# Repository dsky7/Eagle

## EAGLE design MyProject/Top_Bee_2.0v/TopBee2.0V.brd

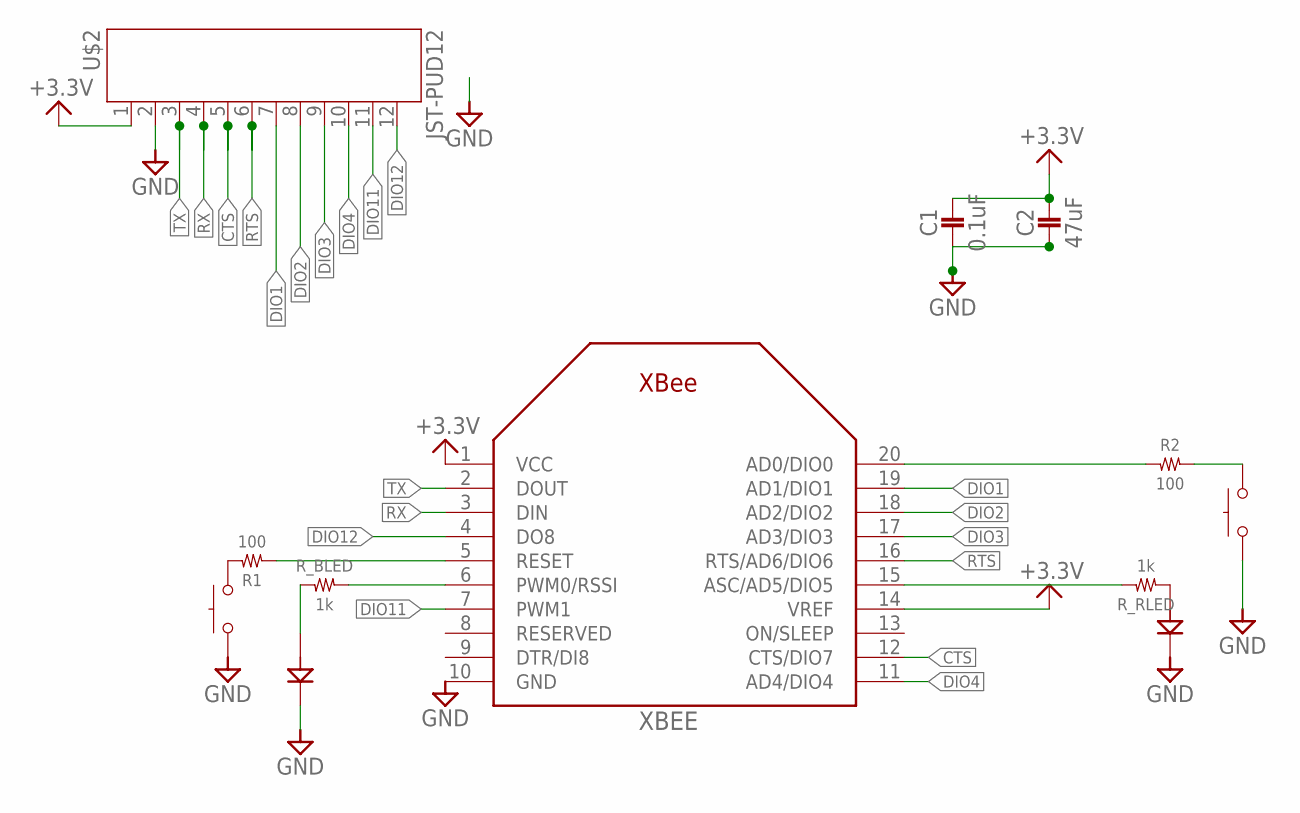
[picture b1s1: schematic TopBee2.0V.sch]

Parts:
C1: 0.1uF; 1608
C2: 47uF; 3225
COMM: SKRPACE010; SKRP
LED_B: 1608
LED_R: 1608
R1, R2: 100; 1608
RESET: SKRPACE010; SKRP
R_BLED: 1k; 1608
R_RLED: 1k; 1608
U$2: JST-PUD12
XBEE: XBEE

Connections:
+3.3V: C1.P$1 (1), C2.P$1 (1), U$2.1, XBEE.1 (VCC), XBEE.14 (VREF)
CTS: U$2.5, XBEE.12 (CTS/DIO7)
DIO1: U$2.7, XBEE.19 (AD1/DIO1)
DIO2: U$2.8, XBEE.18 (AD2/DIO2)
DIO3: U$2.9, XBEE.17 (AD3/DIO3)
DIO4: U$2.10, XBEE.11 (AD4/DIO4)
DIO11: U$2.11, XBEE.7 (PWM1)
DIO12: U$2.12, XBEE.4 (DO8)
GND: C1.P$2 (2), C2.P$2 (2), COMM.3, COMM.4, LED_B.2 (K), LED_R.2 (K), RESET.3, RESET.4, U$2.2, XBEE.10 (GND)
unnamed: LED_R.1 (A), R_RLED.1
unnamed: R2.1, XBEE.20 (AD0/DIO0)
unnamed: R1.1, XBEE.5 (RESET)
unnamed: R1.2, RESET.1, RESET.2
unnamed: COMM.1, COMM.2, R2.2
unnamed: R_BLED.2, XBEE.6 (PWM0/RSSI)
unnamed: R_RLED.2, XBEE.15 (ASC/AD5/DIO5)
unnamed: LED_B.1 (A), R_BLED.1
RTS: U$2.6, XBEE.16 (RTS/AD6/DIO6)
RX: U$2.4, XBEE.3 (DIN)
TX: U$2.3, XBEE.2 (DOUT)

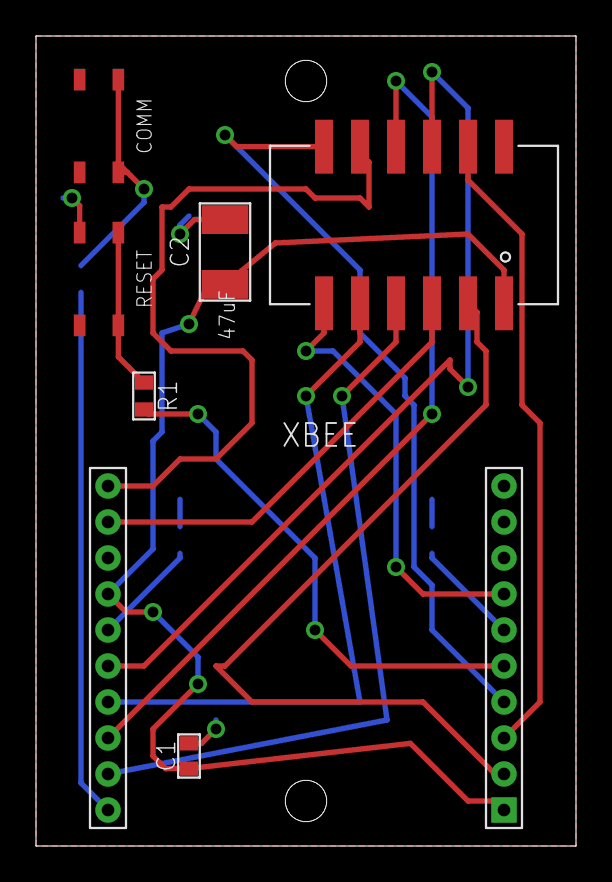
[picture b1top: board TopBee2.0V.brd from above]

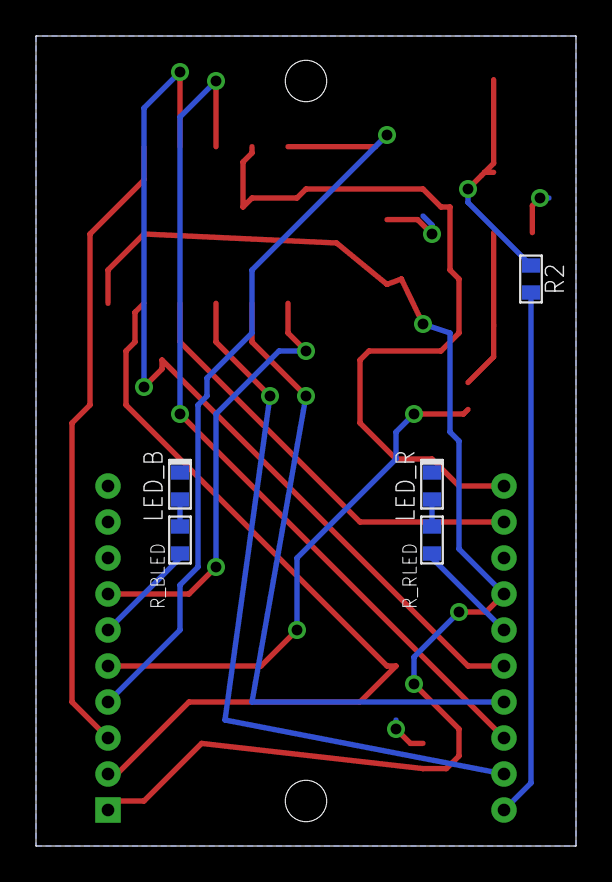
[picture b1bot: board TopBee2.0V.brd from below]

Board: 2 copper layers, 30.0 x 45.0 mm, 12 parts (5 on the bottom side), 20 nets.

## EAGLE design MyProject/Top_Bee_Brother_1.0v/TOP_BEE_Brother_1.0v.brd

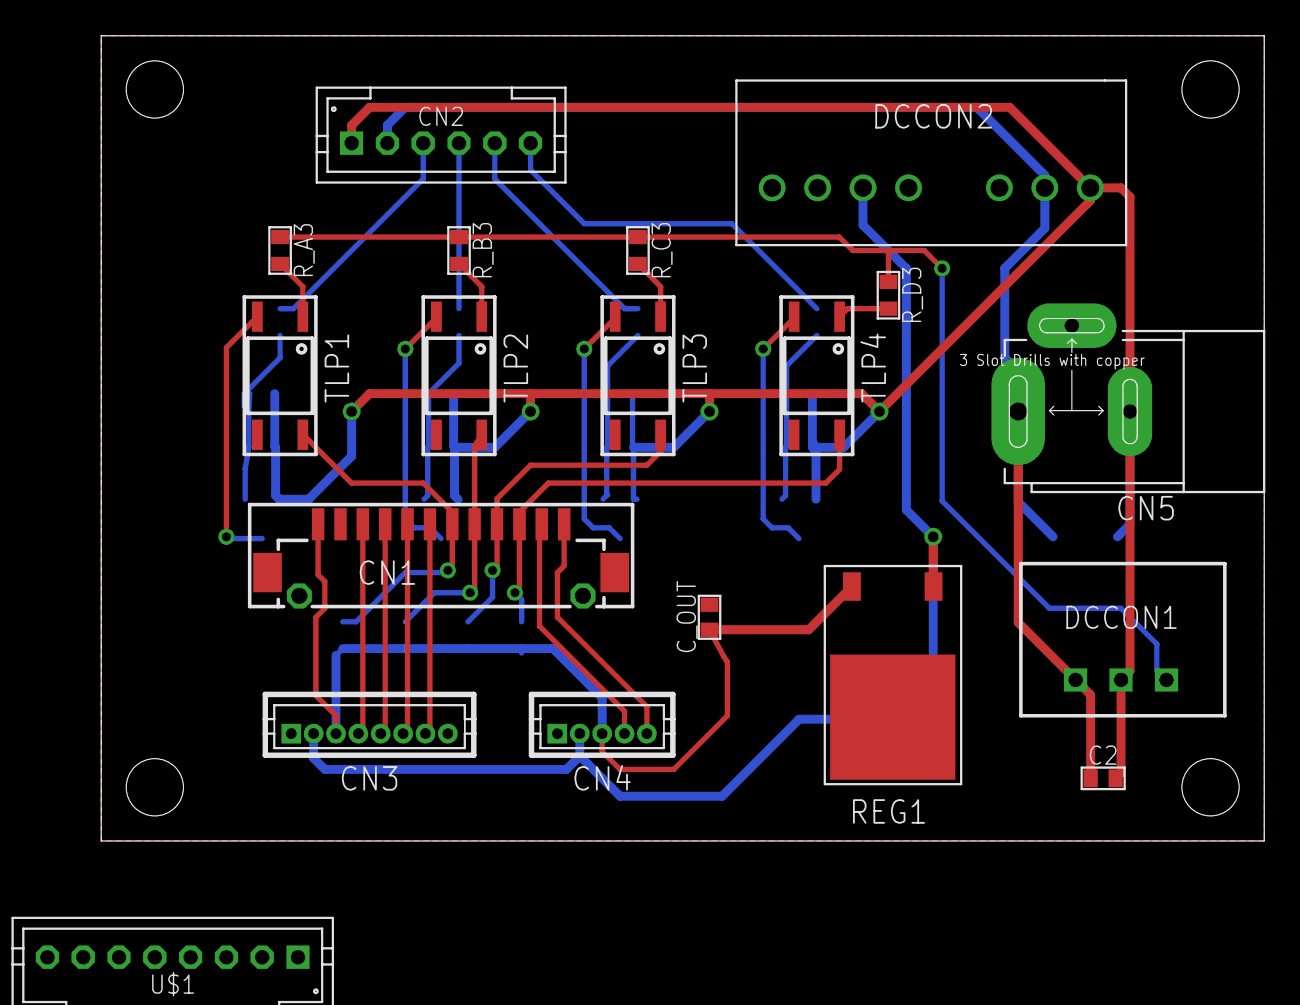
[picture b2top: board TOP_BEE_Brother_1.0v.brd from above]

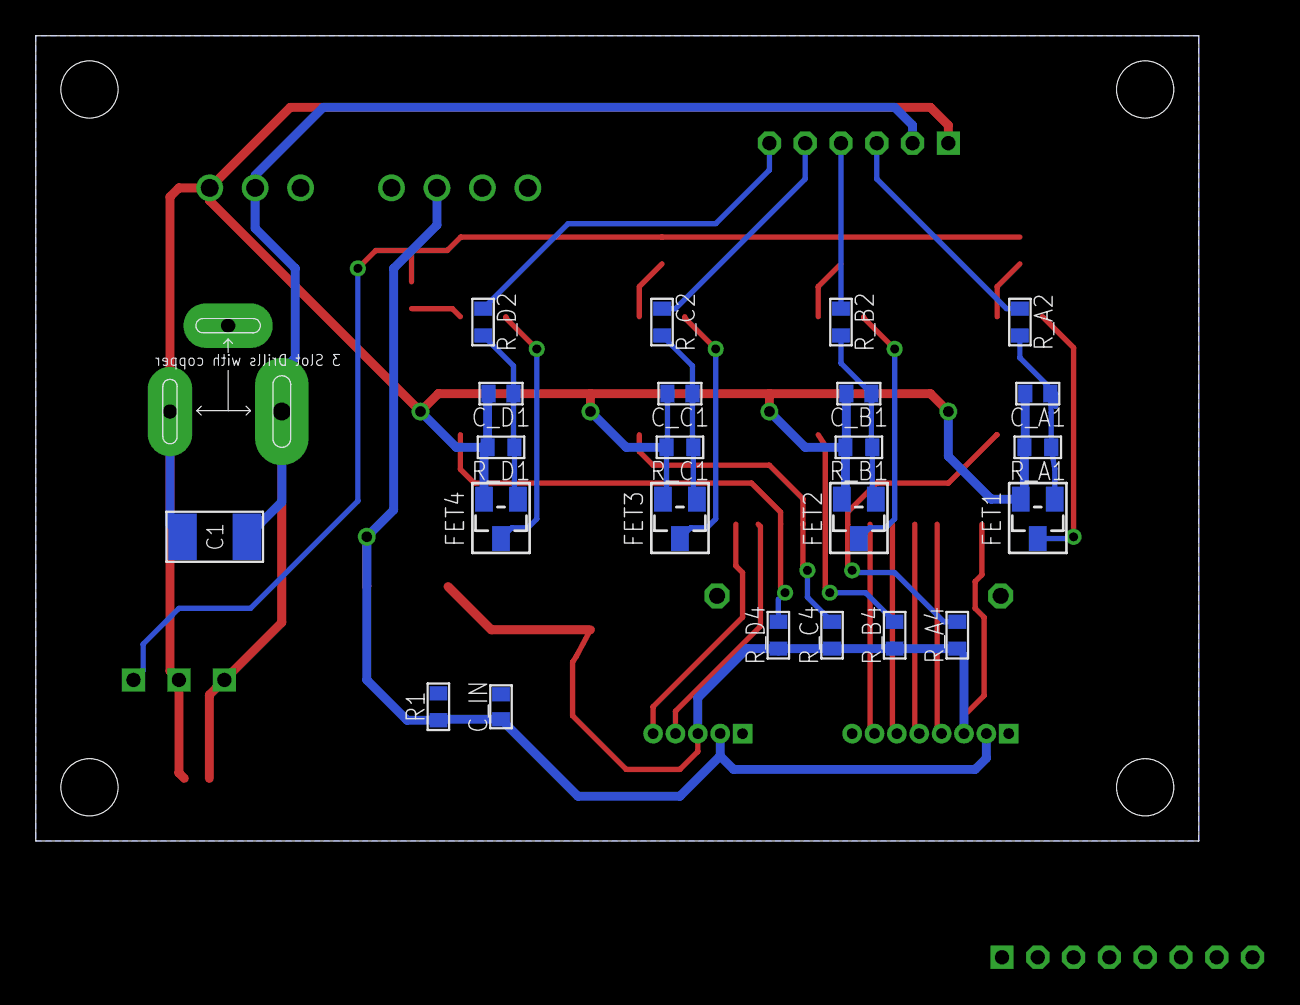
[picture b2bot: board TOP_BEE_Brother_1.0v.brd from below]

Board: 2 copper layers, 65.0 x 45.0 mm, 42 parts (23 on the bottom side), 32 nets.

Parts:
C1: 3225
C2: 1608
CN1: DF13-12P-1.25V; DF13C-12P-1.25V
CN2: JST-PA6
CN3: DF13-8P-1.25DSA
CN4: DF13-5P-1.25DSA
CN5: 2DC-0005X; 2DC-0005D
C_A1: 1608
C_B1: 1608
C_C1: 1608
C_D1: 1608
C_IN: 1608
C_OUT: 1608
DCCON1: Ｒ－７８Ｅ５．０
DCCON2: RS3; SIP8
FET1, FET2, FET3, FET4: 2N7002K; SOT23
R1: 1608
REG1: NJM2845; TO252
R_A1: 4.7K; 1608
R_A2, R_A4: 10k; 1608
R_A3: 330; 1608
R_B1: 4.7K; 1608
R_B2: 10K; 1608
R_B3: 330; 1608
R_B4: 10k; 1608
R_C1: 4.7K; 1608
R_C2: 10K; 1608
R_C3: 330; 1608
R_C4: 10k; 1608
R_D1: 4.7K; 1608
R_D2: 10K; 1608
R_D3: 330; 1608
R_D4: 10k; 1608
TLP1, TLP2, TLP3, TLP4: TLP124; 11−4C1
U$1: JST-PA8

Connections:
2N7002K: C_A1.P$1, FET1.1, R_A1.2, R_A2.1
+3.3V: CN1.P$1, CN3.P$3, CN4.P$3, C_OUT.P$1, REG1.3, R_A4.2, R_B4.2, R_C4.2, R_D4.2
+5V: CN3.P$2, CN4.P$2, C_IN.P$1, DCCON2.6, R1.2, REG1.1
+24V: C1.P$1, C2.P$1, CN2.2, CN5.1, DCCON1.1, DCCON2.2
CTS: CN1.P$5, CN3.P$6
DIO1: CN1.P$7, R_A4.1, TLP1.6
DIO2: CN1.P$8, R_B4.1, TLP2.6
DIO3: CN1.P$9, R_C4.1, TLP3.6
DIO4: CN1.P$10, R_D4.1, TLP4.6
DIO11: CN1.P$11, CN4.P$4
DIO12: CN1.P$12, CN4.P$5
GND: CN1.G1, CN1.G2, CN1.M$0, CN1.M$1, CN1.P$2, CN3.P$1, CN4.P$1, C_IN.P$2, C_OUT.P$2, DCCON2.7, R1.1, REG1.2, TLP1.4, TLP2.4, TLP3.4, TLP4.4
GND2: C1.P$2, C2.P$2, CN2.1, CN5.2, C_A1.P$2, C_B1.P$2, C_C1.P$2, C_D1.P$2, DCCON1.2, DCCON2.1, FET1.2, FET2.2, FET3.2, FET4.2, R_A1.1, R_B1.1, R_C1.1, R_D1.1
INPUT1: CN2.3, R_A2.2
INPUT2: CN2.4, R_B2.2
INPUT3: CN2.5, R_C2.2
INPUT4: CN2.6, R_D2.2
unnamed: FET2.3, TLP2.3
unnamed: FET1.3, TLP1.3
unnamed: R_A3.1, TLP1.1
unnamed: FET4.3, TLP4.3
unnamed: R_B3.1, TLP2.1
unnamed: C_B1.P$1, FET2.1, R_B1.2, R_B2.1
unnamed: FET3.3, TLP3.3
unnamed: R_C3.1, TLP3.1
unnamed: C_C1.P$1, FET3.1, R_C1.2, R_C2.1
unnamed: R_D3.1, TLP4.1
unnamed: C_D1.P$1, FET4.1, R_D1.2, R_D2.1
RTS: CN1.P$6, CN3.P$7
RX: CN1.P$4, CN3.P$5
TX: CN1.P$3, CN3.P$4
V2: DCCON1.3, R_A3.2, R_B3.2, R_C3.2, R_D3.2

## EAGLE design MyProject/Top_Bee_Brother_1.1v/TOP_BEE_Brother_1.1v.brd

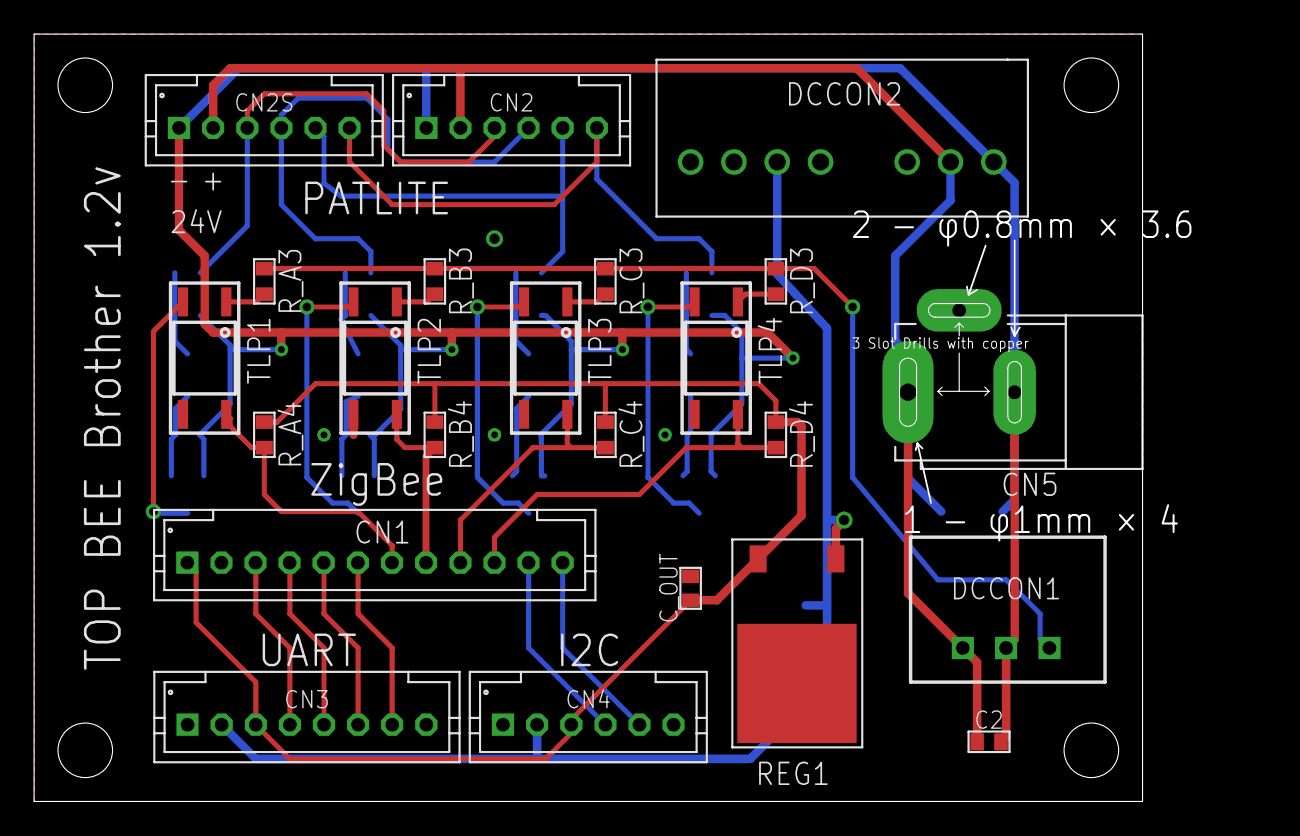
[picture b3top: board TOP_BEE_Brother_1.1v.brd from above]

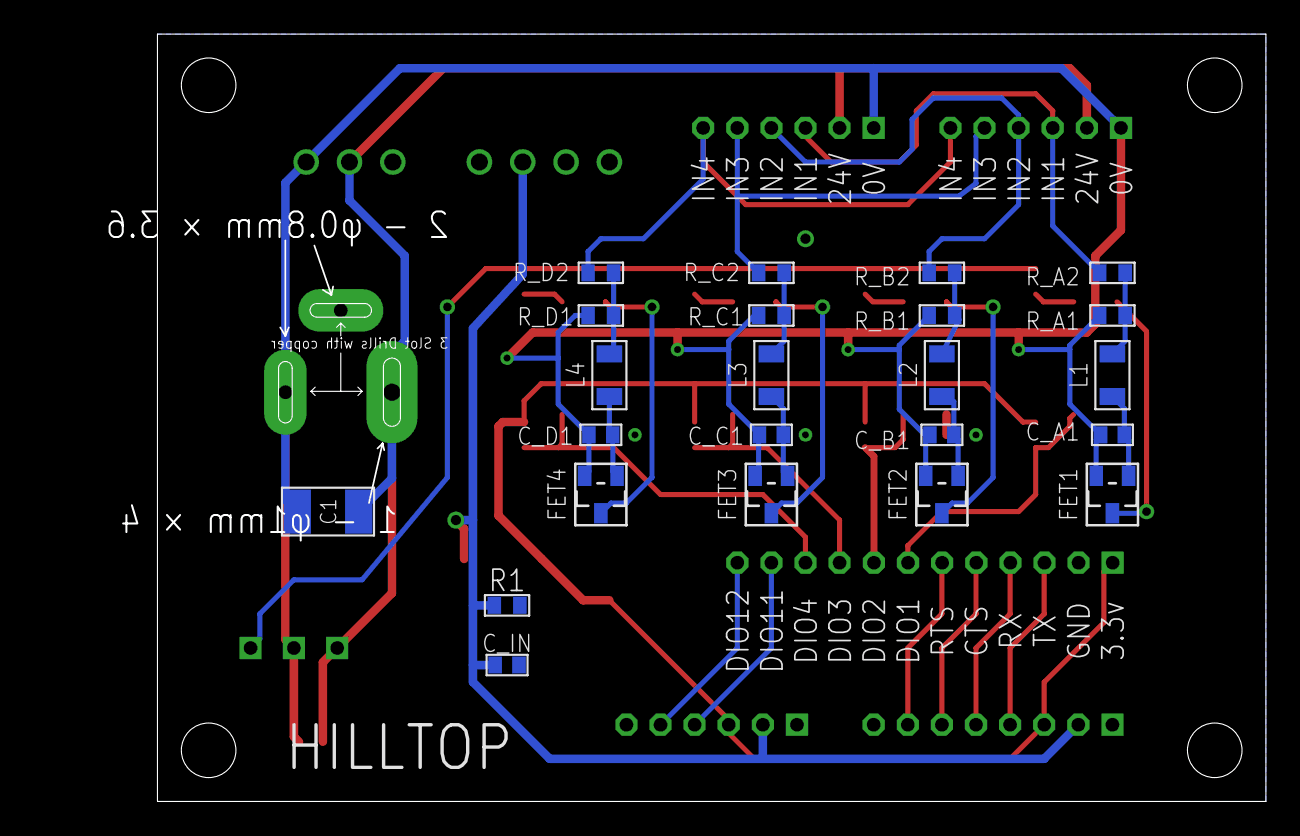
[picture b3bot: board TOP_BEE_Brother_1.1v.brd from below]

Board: 2 copper layers, 65.0 x 45.0 mm, 47 parts (23 on the bottom side), 36 nets.

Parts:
C1: 3225
C2: 1608
CN1: JST-PA12
CN2, CN2S, CN4: JST-PA6
CN3: JST-PA8
CN5: 2DC-0005X; 2DC-0005D
C_A1: 1608
C_B1: 1608
C_C1: 1608
C_D1: 1608
C_IN: 1608
C_OUT: 1608
DCCON1: Ｒ－７８Ｅ５．０
DCCON2: RS3; SIP8
DRILEGEND: DRILEGEND
FET1, FET2, FET3, FET4: 2N7002K; SOT23
L1, L2, L3, L4: TDK_NLV25; TDK_NLV
R1: 1608
REG1: NJM2845; TO252
R_A1: 4.7K; 1608
R_A2, R_A4: 10k; 1608
R_A3: 330; 1608
R_B1: 4.7K; 1608
R_B2: 10K; 1608
R_B3: 330; 1608
R_B4: 10k; 1608
R_C1: 4.7K; 1608
R_C2: 10K; 1608
R_C3: 330; 1608
R_C4: 10k; 1608
R_D1: 4.7K; 1608
R_D2: 10K; 1608
R_D3: 330; 1608
R_D4: 10k; 1608
TLP1, TLP2, TLP3, TLP4: TLP124; 11−4C1

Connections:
2N7002K: L1.P$1, R_A1.2, R_A2.1
+3.3V: CN1.1, CN3.3, CN4.3, C_OUT.P$1, REG1.3, R_A4.2, R_B4.2, R_C4.2, R_D4.2
+5V: CN3.2, CN4.2, C_IN.P$1, DCCON2.6, R1.2, REG1.1
+24V: C1.P$1, C2.P$1, CN2.2, CN2S.2, CN5.1, DCCON1.1, DCCON2.2
CTS: CN1.5, CN3.6
DIO1: CN1.7, R_A4.1, TLP1.6
DIO2: CN1.8, R_B4.1, TLP2.6
DIO3: CN1.9, R_C4.1, TLP3.6
DIO4: CN1.10, R_D4.1, TLP4.6
DIO11: CN1.11, CN4.4
DIO12: CN1.12, CN4.5
GND: CN1.2, CN3.1, CN4.1, C_IN.P$2, C_OUT.P$2, DCCON2.7, R1.1, REG1.2, TLP1.4, TLP2.4, TLP3.4, TLP4.4
GND2: C1.P$2, C2.P$2, CN2.1, CN2S.1, CN5.2, C_A1.P$2, C_B1.P$2, C_C1.P$2, C_D1.P$2, DCCON1.2, DCCON2.1, FET1.2, FET2.2, FET3.2, FET4.2, R_A1.1, R_B1.1, R_C1.1, R_D1.1
INPUT1: CN2.3, CN2S.3, R_A2.2
INPUT2: CN2.4, CN2S.4, R_B2.2
INPUT3: CN2.5, CN2S.5, R_C2.2
INPUT4: CN2.6, CN2S.6, R_D2.2
unnamed: FET2.3, TLP2.3
unnamed: FET1.3, TLP1.3
unnamed: R_A3.1, TLP1.1
unnamed: FET4.3, TLP4.3
unnamed: R_B3.1, TLP2.1
unnamed: L2.P$1, R_B1.2, R_B2.1
unnamed: FET3.3, TLP3.3
unnamed: R_C3.1, TLP3.1
unnamed: L3.P$1, R_C1.2, R_C2.1
unnamed: R_D3.1, TLP4.1
unnamed: L4.P$1, R_D1.2, R_D2.1
unnamed: C_A1.P$1, FET1.1, L1.P$2
unnamed: C_B1.P$1, FET2.1, L2.P$2
unnamed: C_C1.P$1, FET3.1, L3.P$2
unnamed: C_D1.P$1, FET4.1, L4.P$2
RTS: CN1.6, CN3.7
RX: CN1.4, CN3.5
TX: CN1.3, CN3.4
V2: DCCON1.3, R_A3.2, R_B3.2, R_C3.2, R_D3.2

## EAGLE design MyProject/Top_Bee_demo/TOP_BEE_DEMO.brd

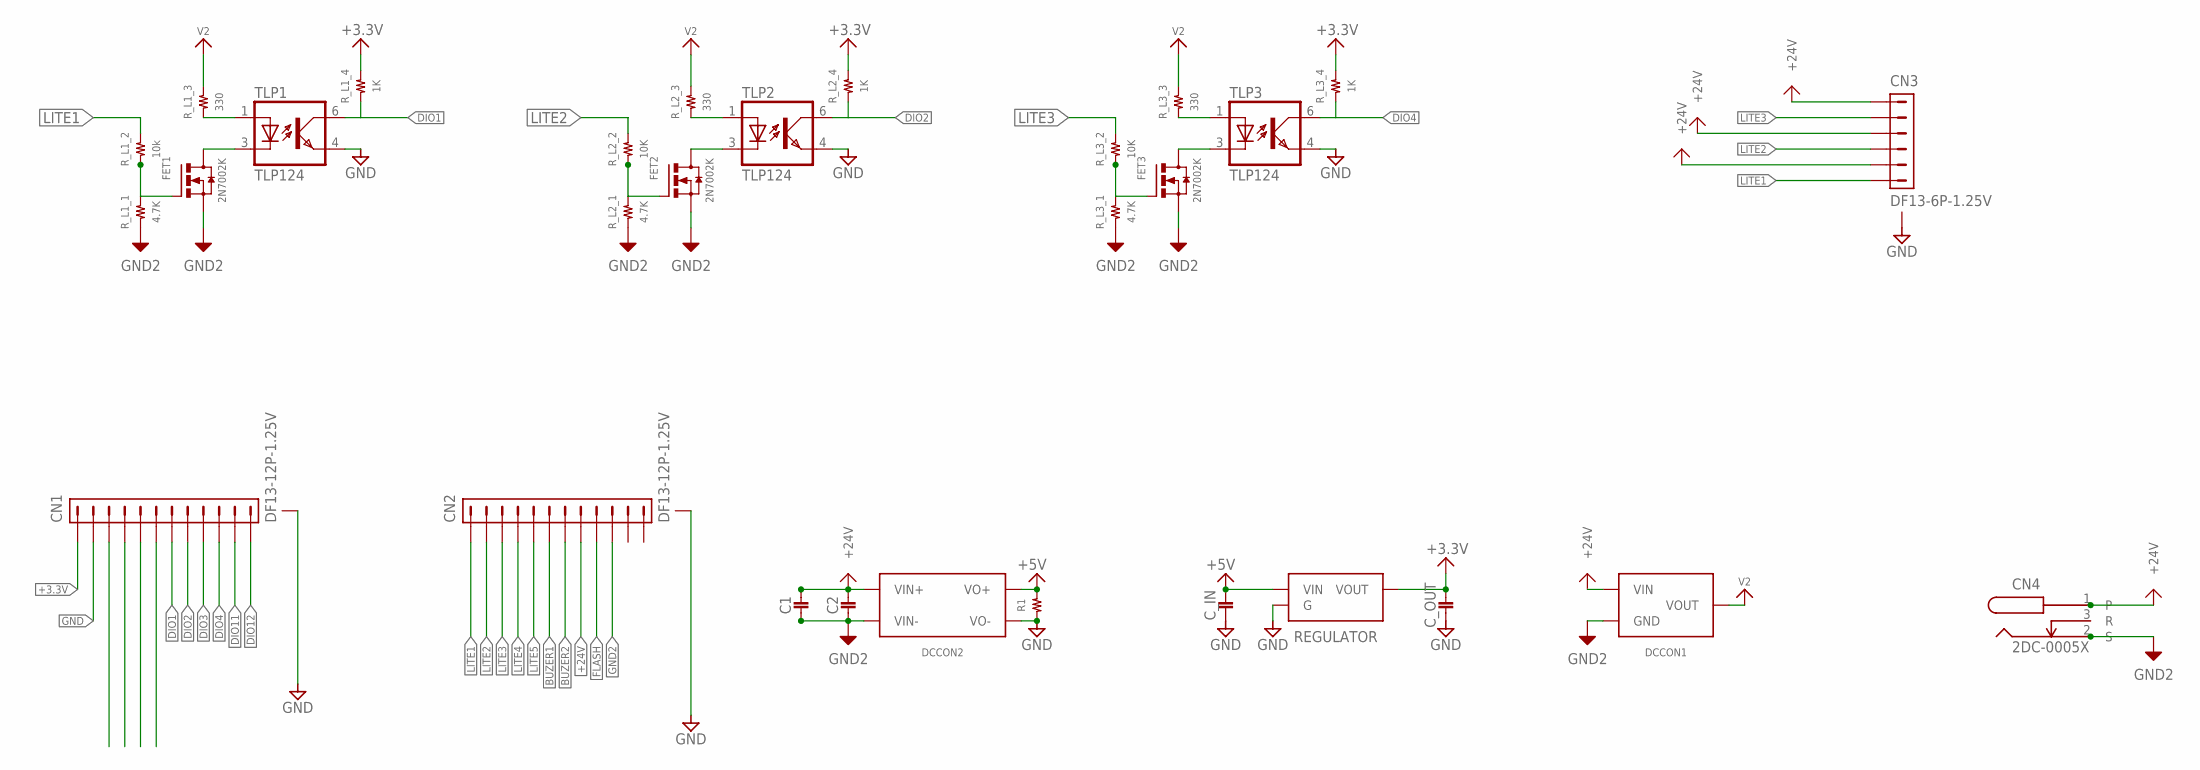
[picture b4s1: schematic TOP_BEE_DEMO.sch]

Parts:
C1: 3225
C2: 1608
CN1, CN2: DF13-12P-1.25V; DF13C-12P-1.25V
CN3: DF13-6P-1.25V; DF13C-6P-1.25V
CN4: 2DC-0005X; 2DC-0005D
C_IN: 1608
C_OUT: 1608
DCCON1: Ｒ－７８Ｅ５．０
DCCON2: MAU100; MAU
FET1, FET2, FET3: 2N7002K; SOT23
R1: RESISTOR__SMD; 1608
REGULATOR: NJM2845; TO252
R_L1_1, R_L2_1, R_L3_1: 4.7K; 1608
R_L1_2: 10k; 1608
R_L1_3, R_L2_3, R_L3_3: 330; 1608
R_L1_4, R_L2_4, R_L3_4: 1K; 1608
R_L2_2, R_L3_2: 10K; 1608
TLP1, TLP2, TLP3: TLP124; 11−4C1

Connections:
2N7002K: FET1.1 (G), R_L1_1.2, R_L1_2.1
+3.3V: CN1.P$1 (1), C_OUT.P$1 (1), REGULATOR.3 (VOUT), R_L1_4.2, R_L2_4.2, R_L3_4.2
+5V: C_IN.P$1 (1), DCCON2.P$5 (VO+), R1.2, REGULATOR.1 (VIN)
+24V: C1.P$1 (1), C2.P$1 (1), CN2.P$8 (8), CN3.P$1 (1), CN3.P$3 (3), CN3.P$5 (5), CN4.1, DCCON1.1 (VIN), DCCON2.P$1 (VIN+)
BUZER1: CN2.P$6 (6)
BUZER2: CN2.P$7 (7)
DIO1: CN1.P$7 (7), R_L1_4.1, TLP1.6 (COL)
DIO2: CN1.P$8 (8), R_L2_4.1, TLP2.6 (COL)
DIO3: CN1.P$9 (9)
DIO4: CN1.P$10 (10), R_L3_4.1, TLP3.6 (COL)
DIO11: CN1.P$11 (11)
DIO12: CN1.P$12 (12)
FLASH: CN2.P$9 (9)
GND: CN1.G1 (G), CN1.G2 (G), CN1.M$0 (G), CN1.M$1 (G), CN1.P$2 (2), CN2.G1 (G), CN2.G2 (G), CN2.M$0 (G), CN2.M$1 (G), CN3.G1 (G), CN3.G2 (G), CN3.M$0 (G), CN3.M$1 (G), C_IN.P$2 (2), C_OUT.P$2 (2), DCCON2.P$3 (VO-), R1.1, REGULATOR.2 (G), TLP1.4 (EMIT), TLP2.4 (EMIT), TLP3.4 (EMIT)
GND2: C1.P$2 (2), C2.P$2 (2), CN2.P$10 (10), CN4.2 (S), DCCON1.2 (GND), DCCON2.P$2 (VIN-), FET1.2 (S), FET2.2 (S), FET3.2 (S), R_L1_1.1, R_L2_1.1, R_L3_1.1
LITE1: CN2.P$1 (1), CN3.P$6 (6), R_L1_2.2
LITE2: CN2.P$2 (2), CN3.P$4 (4), R_L2_2.2
LITE3: CN2.P$3 (3), CN3.P$2 (2), R_L3_2.2
LITE4: CN2.P$4 (4)
LITE5: CN2.P$5 (5)
unnamed: FET2.3 (D), TLP2.3 (C)
unnamed: FET1.3 (D), TLP1.3 (C)
unnamed: R_L1_3.1, TLP1.1 (A)
unnamed: R_L2_3.1, TLP2.1 (A)
unnamed: FET2.1 (G), R_L2_1.2, R_L2_2.1
unnamed: FET3.3 (D), TLP3.3 (C)
unnamed: R_L3_3.1, TLP3.1 (A)
unnamed: FET3.1 (G), R_L3_1.2, R_L3_2.1
V2: DCCON1.3 (VOUT), R_L1_3.2, R_L2_3.2, R_L3_3.2

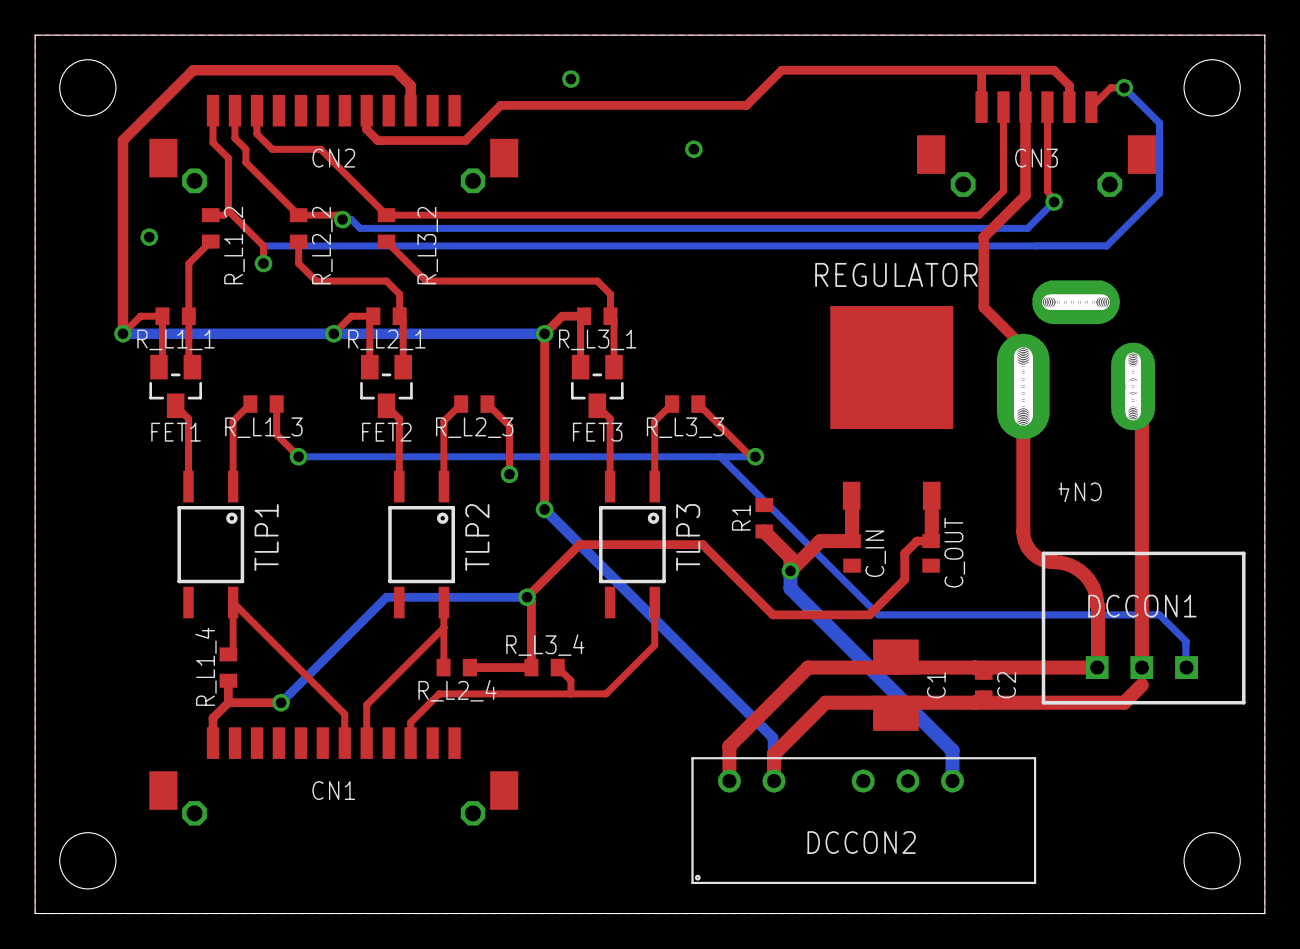
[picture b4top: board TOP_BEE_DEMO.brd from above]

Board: 2 copper layers, 70.0 x 50.0 mm, 30 parts (0 on the bottom side), 21 nets.
